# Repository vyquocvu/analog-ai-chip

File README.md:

# Analog AI Machine

**Design and simulate an analog AI accelerator from first principles — from Ohm's law and SPICE circuits to crossbar tiles, language-model inference, and dedicated pocket hardware appliances.**

The repository is built around one engineering question:

> Can the proposed analog AI architecture plausibly operate as a physical device, and can every system-level parameter be traced back to circuit/device evidence or an explicitly labeled assumption?

The project does not claim silicon verification. It builds a reproducible proof chain:

```text
equation
  ↓
functional reference
  ↓
circuit design
  ↓
ngspice / Xyce
  ↓
validated device profiles
  ↓
profile-driven accelerator
  ↓
Transformer / LLM inference
  ↓
physical feasibility report
  ↓
pocket appliance correlation
```

## Current status

The repository contains a broad functional and simulation chain. R9, R17, and
R18 remain open where physical artifacts or measurements are still missing:

```text
R0 functional + circuit foundation ── COMPLETE
R1 circuit → profile → simulator   ── COMPLETE  (crossbar-column-v1)
R2 converter signal path           ── COMPLETE  (dac-r2r-v1, adc-sar-v1)
R3 small crossbar arrays           ── COMPLETE  (0012 2×2 + 0013 4×4, behavioral-equivalence report)
R4 device realism + crossbar-v1    ── COMPLETE  (crossbar-v1, 2D mesh, variation, IR drop, RC settling, drift/faults)
R5 profile-driven physical tile    ── COMPLETE  (calibrated tile, spatial partial sums, error attribution)
R6 accelerator architecture        ── COMPLETE  (scheduler, SRAM buffers, 2D mesh NoC, unified physical ledger)
R7 Transformer & LLM validation    ── PASSED    (TinyGPT/GPT-2 inference, 3-stage hardware recovery, 129.5 PPL)
R8 physical feasibility report     ── PASSED    (latency 998 ns, energy 29.1 nJ/tok, area 1.412 mm², thermal 30.9°C)
R9 implementation correlation      ── PARTIAL   (FPGA shell; physical PCB/bench evidence pending)
R10 scalable model contract        ── PASSED    (manifest, decoder primitives, sharded checkpoints)
R11 memory-bounded simulator       ── PASSED    (block streaming, sampled/surrogate modes, resumable evaluator)
R12 large-model architecture       ── PASSED    (residency, 2.5D multi-die, prefill/decode, KV hierarchy)
R13 large-model validation         ── PASSED    (frozen corpus eval, error attribution, scalable recovery suite)
R14 multi-tier feasibility         ── PASSED    (parametric ledger, Pareto sweeps, 28nm tape-out decision)
R15 physical layout & DRC/LVS      ── PARTIAL   (geometric models; connectivity LVS and physical signoff pending)
R16 post-layout PEX & STA signoff  ── PARTIAL   (assumed analytical models; corrected settling misses aperture)
R17 tape-out & package/PCB signoff ── PARTIAL   (analytical models; physical artifacts pending)
R18 pocket AI communicator / pager ── PARTIAL   (placeholder carrier; electrical implementation incomplete)
```

The strongest claims and their remaining evidence gaps are tracked in
[`docs/ROADMAP.md`](docs/ROADMAP.md) and
[`docs/CURRICULUM.md`](docs/CURRICULUM.md).

---

## Pocket Analog AI Communicator (Pager-1)

Gate R18 implements the dedicated offline text appliance concept: an ultra-low-power pocket communicator ("AI Pager / Beeper") that couples a digital host controller with a 28nm ReRAM Analog Compute-in-Memory Neural Engine.

| Parameter | Specification | Real-World Significance |
| :--- | :--- | :--- |
| **Chassis & Form Factor** | $72.0 \times 54.0 \times 14.5\text{ mm}$ ($85\text{ g}$) | CNC anodized aluminum 6061-T6 with spring-steel belt clip |
| **Reflective Display** | 2.7" Sharp LS027B7DH01 ($400 \times 240$) | Sharp lists **$175\,\mu\text{W}$** for its specified update pattern; standby remains assumed |
| **Input Subsystem** | 35-key tactile QWERTY + Jog Dial | Metal dome tactile switches ($160\text{ gf}$) with I2C scanner (`TCA8418`) |
| **Host Controller** | STM32U575VGT6 Cortex-M33 | Rev A selection; local tokenization and accelerator framing |
| **Battery Autonomy** | $1200\text{ mAh}$ Li-Po ($4.44\text{ Wh}$) | Representative budget: **958 days standby**, **99.8 hours active**; hardware validation pending |
| **Thermal Dissipation** | $25.4^\circ\text{C}$ surface temperature | 100% natural passive convection ($<45.0^\circ\text{C}$ skin touch limit) |
| **Bench Correlation** | Pending | Existing numerical sweep is representative synthetic data, not a measurement |

### Hardware Architecture & Silicon Teardown

---

## Engineering hierarchy

```text
Math / ideal reference
        ↓
Circuit primitives
        ↓
SPICE-verified current-mode crossbar
        ↓
Circuit-to-profile extraction
        ↓
DAC / ADC signal path
        ↓
Small crossbar arrays
        ↓
Device realism + variation
        ↓
Profile-driven tile
        ↓
Multi-tile accelerator + data movement
        ↓
Transformer / LLM mapping
        ↓
Latency / energy / area feasibility
        ↓
FPGA / PCB / silicon correlation
```

See [`docs/CURRICULUM.md`](docs/CURRICULUM.md) for the canonical chapter sequence and [`docs/ROADMAP.md`](docs/ROADMAP.md) for implementation gates.

## Simulation stack

- **KiCad** — schematic and later PCB/layout design artifacts.
- **ngspice** — default SPICE backend for circuit verification, sweeps, transient/noise analysis and compact models.
- **PySpice** — Python automation, assertions, extraction and reproducible experiment orchestration.
- **Xyce** — large-array / parallel SPICE backend when ngspice becomes impractical.
- **NumPy / PyTorch** — functional references, architecture simulation, model mapping and accuracy studies.

See [`docs/SIMULATION_STACK.md`](docs/SIMULATION_STACK.md).

---

## Track 1 — Sequential design book (`book/`)

| # | Topic | Status | Path |
|---|---|---|---|
| 0000 | System and verification boundaries | done | `book/0000-what-we-are-building/` |
| 0001 | Ohm + Kirchhoff = MVM | done | `book/0001-crossbar-mvm/` |
| 0002 | Signed differential weights | done | `book/0002-differential-pairs/` |
| 0003 | DAC/ADC quantization and noise | done | `book/0003-converters-and-noise/` |
| 0004 | Tiling a matrix across arrays | done | `book/0004-tiling/` |
| 0005 | One analog neuron — SPICE | done | `book/0005-one-analog-neuron/` |
| 0006 | Many neurons / scaling | done | `book/0006-many-neurons/` |
| 0007 | Current-mode differential crossbar column | done | `book/0007-crossbar-column/` |
| 0008 | Circuit evidence → device profile | done | `verification/circuit/` + `device_profiles/` |
| 0009 | DAC architecture | done | `book/0009-dac-r2r/` |
| 0010 | ADC / TIA output path | done | `book/0010-adc-sar/` |
| 0011 | Converter variation | done | `book/0011-converter-variation/` |
| 0012 | 2×2 differential crossbar | done | `book/0012-crossbar-2x2/` |
| 0013 | 4×4 differential crossbar | done | `book/0013-crossbar-4x4/` |
| 0014 | Array timing and loading | done | `book/0014-array-timing/` |
| 0015 | Programmable conductance compact model | done | `book/0015-conductance-model/` |
| 0016 | Programming and read variation | done | `book/0016-variation/` |
| 0017 | IR drop and line resistance | done | `book/0017-ir-drop/` |
| 0018 | Parasitic capacitance and RC settling | done | `book/0018-parasitics/` |
| 0019 | Drift, stuck states and non-linearity | done | `book/0019-drift-faults/` |
| 0020 | Crossbar-v1 profile and Gate R4 close | done | `book/0020-crossbar-v1/` |
| 0021 | Physical tile contract | done | `book/0021-physical-tile-contract/` |
| 0022 | Partial sums | done | `book/0022-partial-sums/` |
| 0023 | Scheduler and temporal reuse | done | `book/0023-scheduler/` |
| 0046 | Architecture-neutral model manifest | done | `book/0046-model-manifest/` |
| 0047 | Reusable decoder primitives | done | `book/0047-decoder-primitives/` |
| 0068 | PCIe Gen5 evaluation carrier board signoff | done | `book/0068-pcie-gen5-carrier-board-signoff/` |
| 0069 | Pager-1 product architecture & power ledger | done | `book/0069-pager-product-architecture/` |
| 0070 | Host-to-CiM binary packet protocol & runtime | done | `book/0070-pager-packet-protocol/` |
| 0071 | Pocket carrier PCB & bench correlation | done | `book/0071-pager-hardware-correlation/` |

> See [`docs/CURRICULUM.md`](docs/CURRICULUM.md) for the complete index of all 72 chapters (0000–0071). Every chapter has a bilingual `README.vi.md` beside `README.md`.

## Track 2 — Analog LLM architecture simulator (`analog_llm/`)

A decoder-only transformer runs end to end in software. Dense matrix-vector operations are routed through simulated crossbar tiles; layer norm, softmax, GELU, residual/bias operations and embeddings remain digital.

```text
Prompt tokens
     ↓
Token embedding (digital table)
     ↓
┌────────────────────────────────────────────────────────┐
│ Transformer layer × N                                  │
│   ├── RMSNorm / LayerNorm (digital FP32)               │
│   ├── QKV projection (analog CrossbarTiles)            │
│   ├── Scaled dot-product attention + KV cache (digital)│
│   ├── Output projection (analog CrossbarTiles)         │
│   ├── Residual addition (digital FP32)                 │
│   ├── RMSNorm / LayerNorm (digital FP32)               │
│   ├── MLP / Feed-Forward up+gate (analog CrossbarTiles)│
│   ├── GELU / SiLU activation (digital FP32)            │
│   ├── MLP down projection (analog CrossbarTiles)       │
│   └── Residual addition (digital FP32)                 │
└────────────────────────────────────────────────────────┘
     ↓
Final norm + LM head (analog or digital)
     ↓
Greedy / top-p sampler → next token
```

## Track 3 — Device profiles (`device_profiles/`)

Every physical claim made by the simulator must consume a machine-readable profile derived from KiCad/ngspice/Xyce verification, a validated analytical derivation, or an explicitly stated sensitivity-study assumption.

Evidence classes:

- `measured` — physical hardware measurement;
- `spice` — extracted from a named circuit simulation;
- `derived` — calculated from traceable evidence;
- `assumed` — sensitivity-study input only.

The repository contains the validated SPICE-backed profiles `crossbar-column-v1`, `crossbar-v1`, `dac-r2r-v1` and `adc-sar-v1`, all consumed by `analog_llm` through `profile_adapter` (fail-closed: `assumed`/functional-only evidence cannot support a physical claim). The active milestone is the architecture-neutral model contract and checkpoint-ingestion path for larger models (roadmap R10).

## Verification evidence

Preferred evidence chain:

```text
source schematic/netlist/model
      + deterministic script
      + machine-readable result
      + generated figure
      + validated device profile
      + downstream consumer test
```

A plot without reproducible source/result data is not sufficient evidence.

## Python Environment Setup Guide

### 1. Prerequisites
- **Python 3.9+** (`python3 --version`)
- **Git** (`git --version`)
- *(Optional for circuit SPICE sweeps)*: `ngspice` / `libngspice`

### 2. Step-by-Step Installation

#### Step 1: Clone the repository
```bash
git clone https://github.com/vyquocvu/analog-ai-chip.git
cd analog-ai-chip
```

#### Step 2: Create and activate a virtual environment
- **macOS / Linux**:
  ```bash
  python3 -m venv .venv
  source .venv/bin/activate
  ```
- **Windows (PowerShell)**:
  ```powershell
  python -m venv .venv
  .venv\Scripts\Activate.ps1
  ```

#### Step 3: Install Python dependencies

Choose the target configuration for your workflow:

- **Core & Development** (Unit tests, linter, NumPy, model simulation):
  ```bash
  pip install --upgrade pip
  pip install -e '.[dev]'
  ```

- **Full Simulation Stack** (Adds PySpice for circuit simulation and extraction):
  ```bash
  pip install -e '.[dev,sim]'
  ```

#### Step 4: (Optional) Install `ngspice` for Circuit Simulation
If running or extracting SPICE netlists (`book/0005`–`0014`, `verification/circuit/`):

- **macOS (Homebrew)**:
  ```bash
  brew install libngspice ngspice
  ```
  *(The codebase automatically detects `/opt/homebrew/lib/libngspice.dylib` or `/usr/local/lib/libngspice.dylib`)*

- **Ubuntu / Debian**:
  ```bash
  sudo apt-get update && sudo apt-get install -y libngspice0-dev ngspice
  ```

### 3. Verify Installation

Run the test suite and quality checks:
```bash
# 1. Run all unit tests (233 tests across math, circuits, profiles, and LLM)
pytest

# 2. Run code style & static analysis
ruff check .

# 3. Execute the profile-driven TinyGPT analog accelerator simulation
python scripts/run_llm_sim.py
```

## Honesty principles

- Keep *functional*, *circuit/device*, and *system* claims separate.
- Never describe NumPy/PyTorch execution as physical analog acceleration.
- Never infer end-to-end `O(1)` latency from one resident crossbar operation.
- Never turn an assumed ADC/crossbar parameter into a verified hardware claim.
- Every feasibility report must identify what is simulated, derived, assumed, and measured.

Until physical measurements exist, the strongest supported status is **simulation-backed physical feasibility**, not silicon verification.

## License

MIT. See [LICENSE](LICENSE).

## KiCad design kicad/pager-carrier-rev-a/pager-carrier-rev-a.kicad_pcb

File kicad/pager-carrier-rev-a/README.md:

# Pager-1 Carrier Rev A

This directory contains the editable KiCad 10 source for the 70 mm × 52 mm,
four-layer Pager-1 main carrier. The display, keypad, protected Li-Po pack, and
analog accelerator are external assemblies.

## Evidence boundary

Status: `INCOMPLETE_CARRIER_DESIGN`. Do not fabricate this placeholder as a
working product. Subsystem sheets contain text only, most components are
unconnected, and generated footprints do not implement the declared packages.
The BOM lacks the PMIC inductor and capacitors. Clean ERC/DRC on passive,
no-connect symbols does not establish electrical completeness.

The historical evidence record omits subsheets and local libraries and is now
rejected by the source-inventory check. Manufacturing export is also blocked by
BOM footprint mismatches. The preliminary impedance estimate remains `assumed`.
See `SOURCE_NOTES.md` for manufacturer references; startup and pin assignments
still require circuit implementation and verification.

The authoritative electrical/mechanical contract is
`hardware-manifest.json`. In particular, pins named `NC_RESERVED_*` must not be
connected and pins named `TEST_ONLY_*` are diagnostic inputs, not production
interfaces.

## Project files

- `pager-carrier-rev-a.kicad_pro`: project settings.
- `pager-carrier-rev-a.kicad_sch`: hierarchy overview.
- `power.kicad_sch`, `host.kicad_sch`, `display.kicad_sch`,
  `input-haptics.kicad_sch`, `accelerator-mezzanine.kicad_sch`: subsystem
  text-only placeholder sheets.
- `pager-carrier-rev-a.kicad_pcb`: partially routed placeholder layout.
- `pager-carrier-rev-a.kicad_dru`: project design rules.
- `Pager.kicad_sym`, `Pager.pretty/`, and the library tables: project-local
  source for the custom connector symbol and land pattern. Project schematics
  and the routed board also embed their generated library copies.

## Validation and manufacturing exports

KiCad 10.0.x is required. Run:

```bash
python scripts/build_pager_kicad.py --kicad-cli /path/to/kicad-cli
```

The command runs ERC and DRC with violation exit codes, exports BOM, Gerbers,
drill and placement data, PDF documentation, STEP, and front/back renders,
then writes a deterministic release manifest beneath `build/kicad/pager-carrier-rev-a/`.
Generated manufacturing files are intentionally not committed.

## Power-up constraint

BQ25120A starts its SYS buck at 1.8 V. Firmware must boot from internal MCU
flash, program SYS to 3.3 V, verify it, and only then enable the switched 2.5 V,
1.0 V, and LCD 5 V rails. `ACCEL_RESET_N` remains asserted during this sequence.

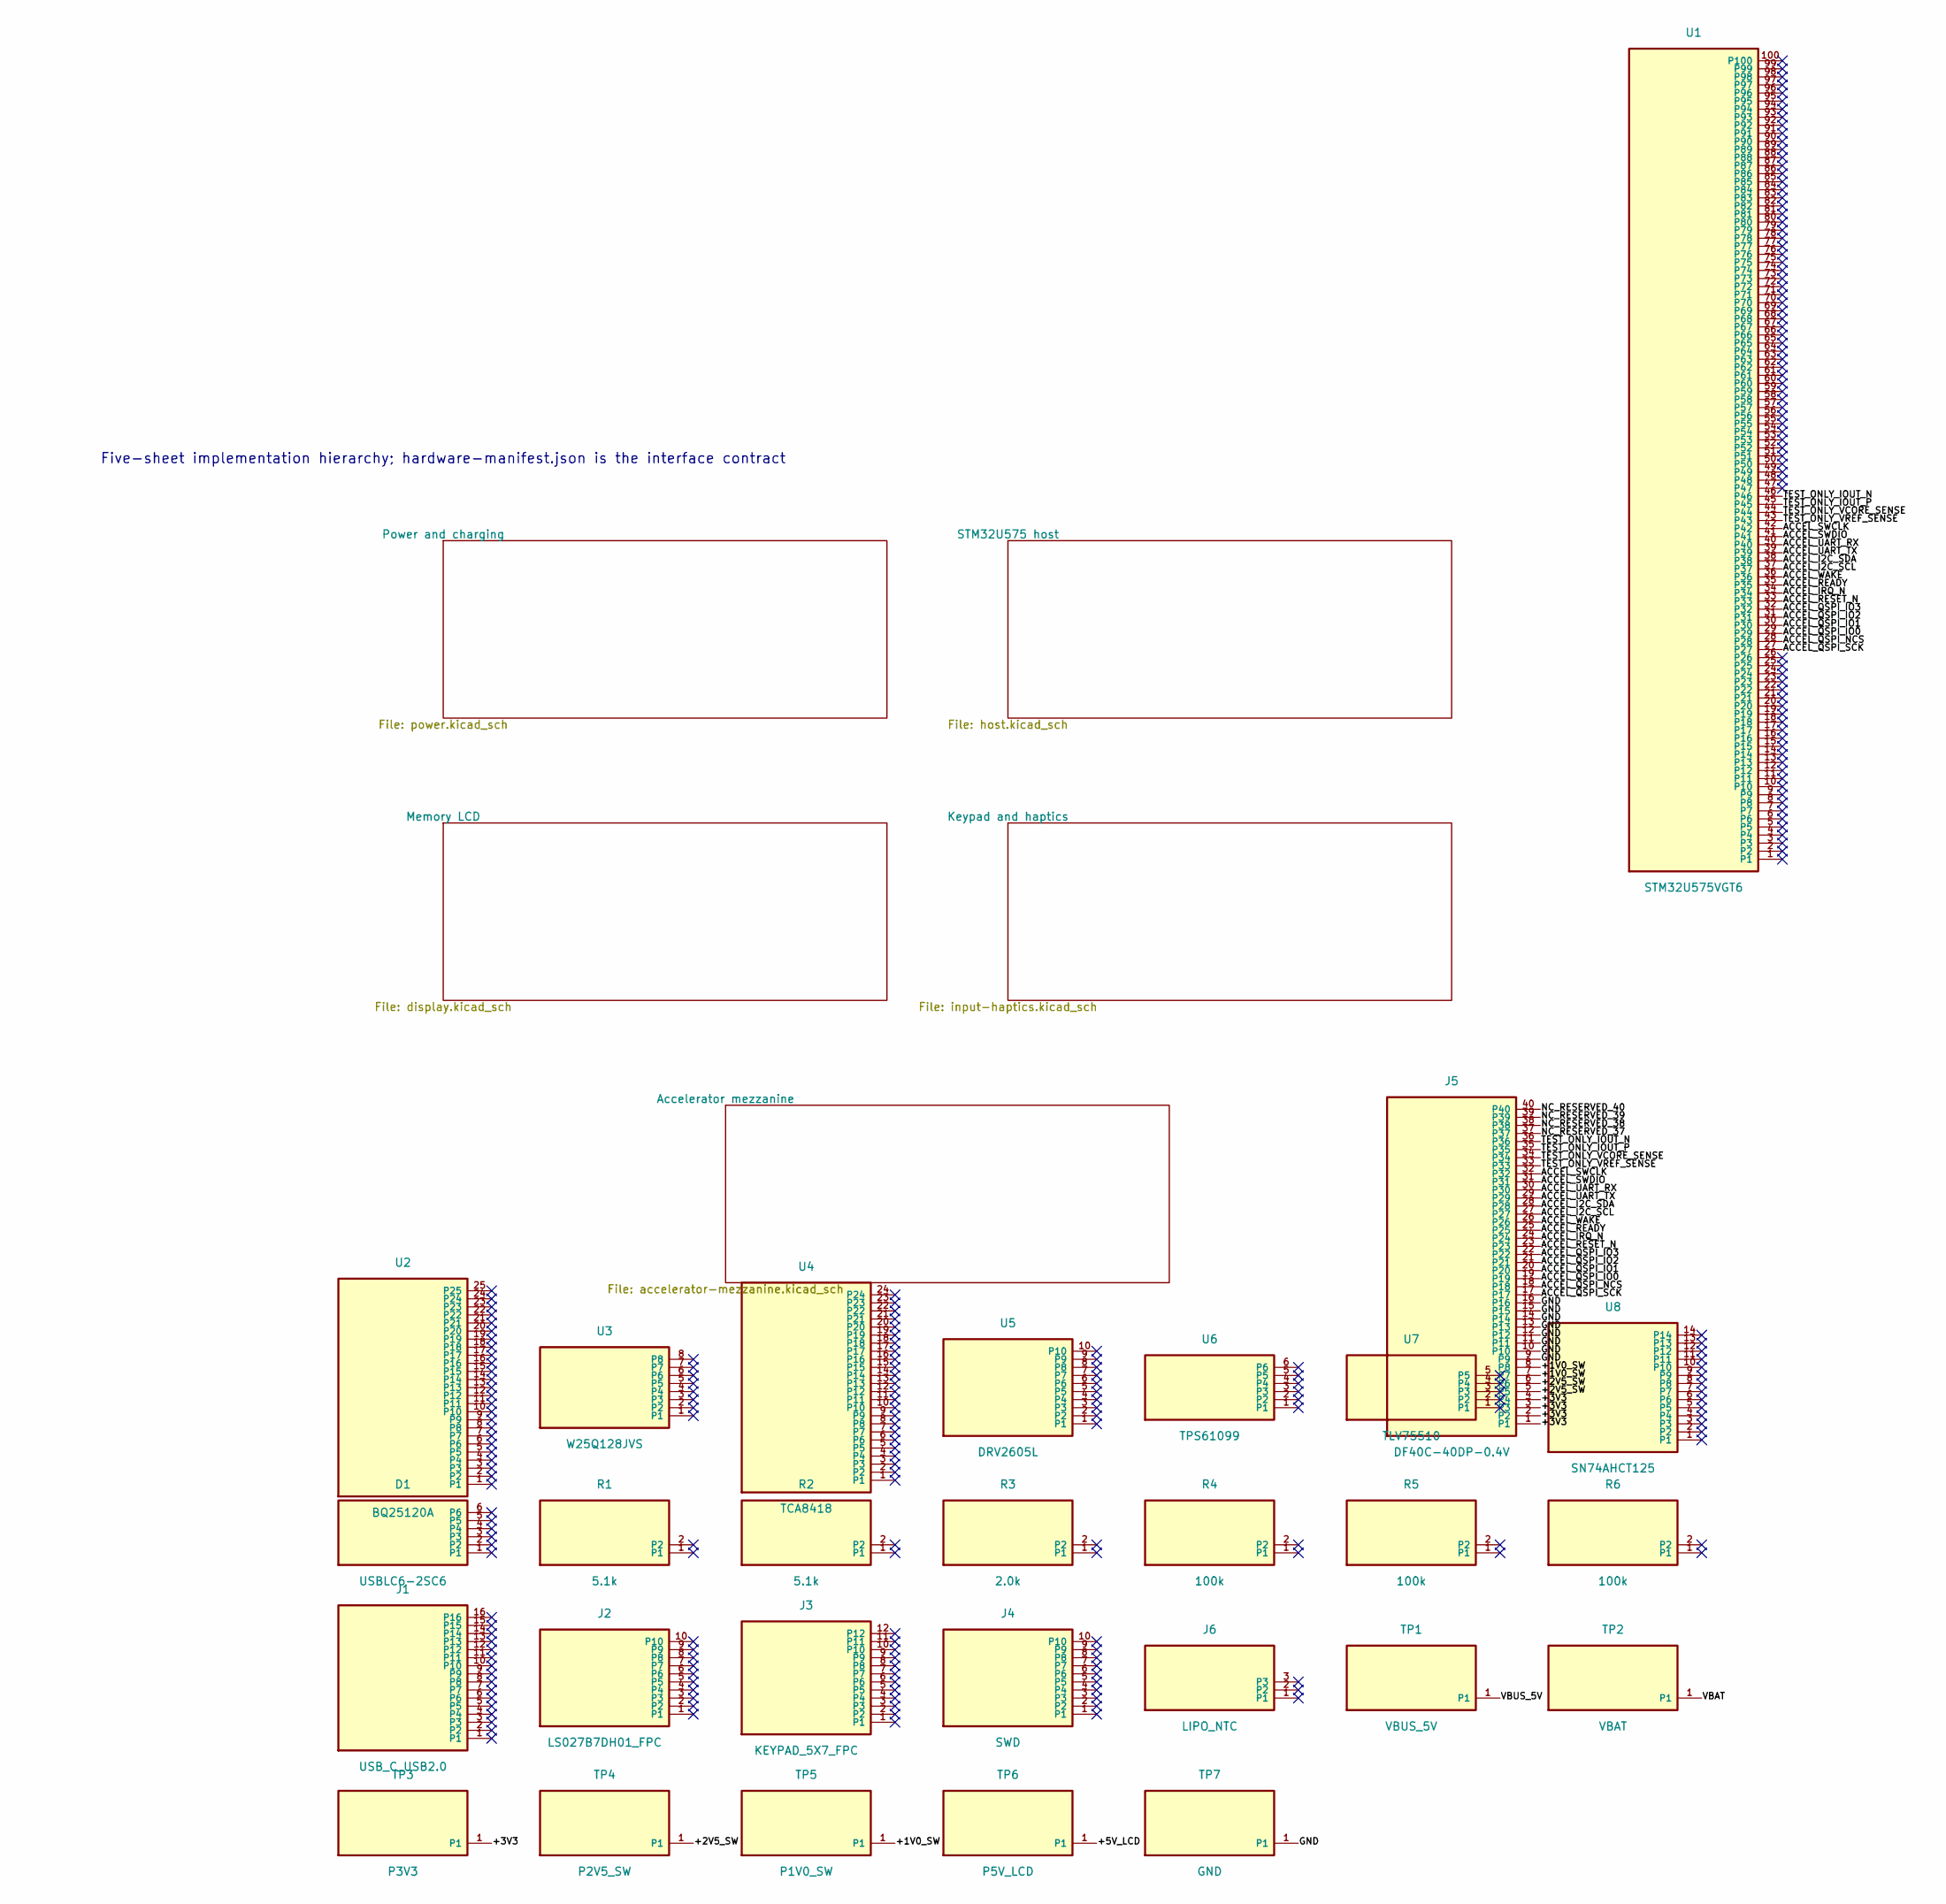
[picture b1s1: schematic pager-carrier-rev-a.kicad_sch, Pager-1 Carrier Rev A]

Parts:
D1: USBLC6-2SC6; MPN USBLC6-2SC6
J1: USB_C_USB2.0; MPN USB4105-GF-A
J2: LS027B7DH01_FPC; MPN FH12-10S-0.5SH(55)
J3: KEYPAD_5X7_FPC; MPN FH12-12S-0.5SH(55)
J4: SWD; MPN FTSH-105-01-L-DV-K
J5: DF40C-40DP-0.4V; MPN DF40C-40DP-0.4V(51)
J6: LIPO_NTC; MPN S3B-PH-K-S
R1, R2: 5.1k; MPN RC0402FR-075K1L
R3: 2.0k; MPN RC0402FR-072KL
R4, R5, R6: 100k; MPN RC0402FR-07100KL
TP1: VBUS_5V
TP2: VBAT
TP3: P3V3
TP4: P2V5_SW
TP5: P1V0_SW
TP6: P5V_LCD
TP7: GND
U1: STM32U575VGT6; MPN STM32U575VGT6
U2: BQ25120A; MPN BQ25120AYFPR
U3: W25Q128JVS; MPN W25Q128JVSIQ
U4: TCA8418; MPN TCA8418RTWR
U5: DRV2605L; MPN DRV2605LDGSR
U6: TPS61099; MPN TPS61099DRVR
U7: TLV75510; MPN TLV75510PDBVR
U8: SN74AHCT125; MPN SN74AHCT125PWR

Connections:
/+1V0_SW: J5.7, J5.8, TP5.1
/+2V5_SW: J5.5, J5.6, TP4.1
/+3V3: J5.1, J5.2, J5.3, J5.4, TP3.1
/+5V_LCD: TP6.1
/ACCEL_I2C_SCL: J5.27, U1.37
/ACCEL_I2C_SDA: J5.28, U1.38
/ACCEL_IRQ_N: J5.24, U1.34
/ACCEL_QSPI_IO0: J5.19, U1.29
/ACCEL_QSPI_IO1: J5.20, U1.30
/ACCEL_QSPI_IO2: J5.21, U1.31
/ACCEL_QSPI_IO3: J5.22, U1.32
/ACCEL_QSPI_NCS: J5.18, U1.28
/ACCEL_QSPI_SCK: J5.17, U1.27
/ACCEL_READY: J5.25, U1.35
/ACCEL_RESET_N: J5.23, U1.33
/ACCEL_SWCLK: J5.32, U1.42
/ACCEL_SWDIO: J5.31, U1.41
/ACCEL_UART_RX: J5.30, U1.40
/ACCEL_UART_TX: J5.29, U1.39
/ACCEL_WAKE: J5.26, U1.36
/GND: J5.9, J5.10, J5.11, J5.12, J5.13, J5.14, J5.15, J5.16, TP7.1
/NC_RESERVED_37: J5.37
/NC_RESERVED_38: J5.38
/NC_RESERVED_39: J5.39
/NC_RESERVED_40: J5.40
/TEST_ONLY_IOUT_N: J5.36, U1.46
/TEST_ONLY_IOUT_P: J5.35, U1.45
/TEST_ONLY_VCORE_SENSE: J5.34, U1.44
/TEST_ONLY_VREF_SENSE: J5.33, U1.43
/VBAT: TP2.1
/VBUS_5V: TP1.1

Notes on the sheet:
Five-sheet implementation hierarchy; hardware-manifest.json is the interface contract

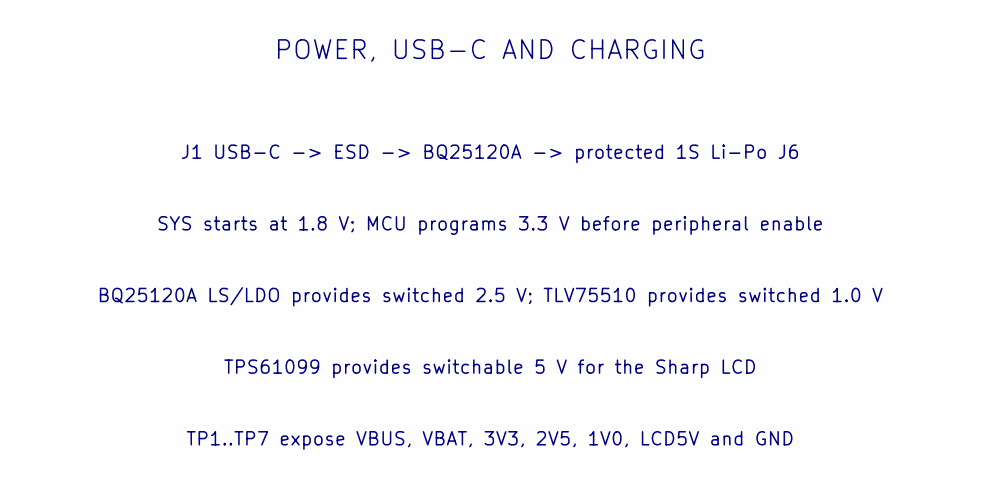
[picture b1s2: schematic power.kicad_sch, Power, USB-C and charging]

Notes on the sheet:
POWER, USB-C AND CHARGING
J1 USB-C -> ESD -> BQ25120A -> protected 1S Li-Po J6
SYS starts at 1.8 V; MCU programs 3.3 V before peripheral enable
BQ25120A LS/LDO provides switched 2.5 V; TLV75510 provides switched 1.0 V
TPS61099 provides switchable 5 V for the Sharp LCD
TP1..TP7 expose VBUS, VBAT, 3V3, 2V5, 1V0, LCD5V and GND

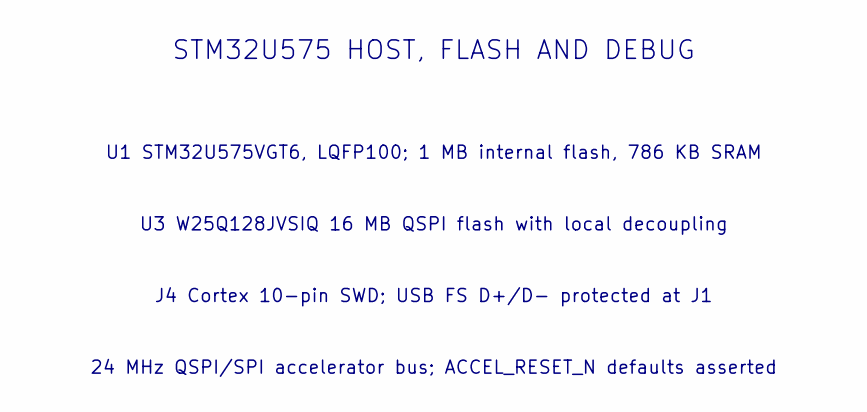
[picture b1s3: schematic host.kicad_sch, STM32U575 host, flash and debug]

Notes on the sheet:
STM32U575 HOST, FLASH AND DEBUG
U1 STM32U575VGT6, LQFP100; 1 MB internal flash, 786 KB SRAM
U3 W25Q128JVSIQ 16 MB QSPI flash with local decoupling
J4 Cortex 10-pin SWD; USB FS D+/D- protected at J1
24 MHz QSPI/SPI accelerator bus; ACCEL_RESET_N defaults asserted

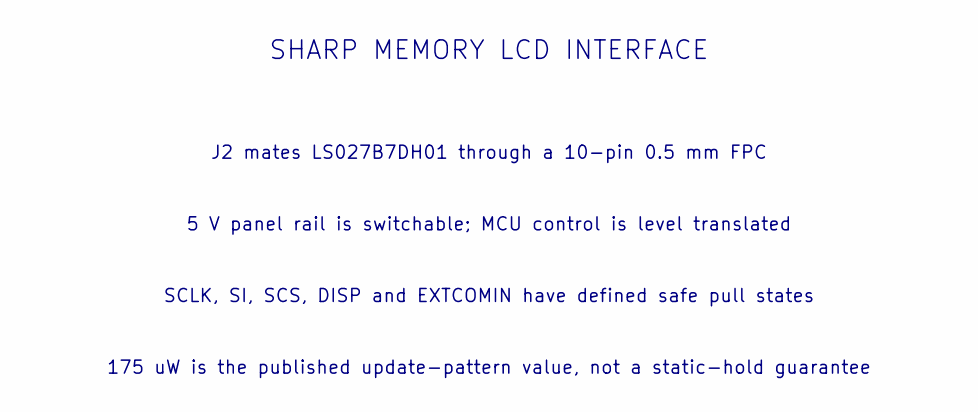
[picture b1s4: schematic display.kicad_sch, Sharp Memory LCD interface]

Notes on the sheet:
SHARP MEMORY LCD INTERFACE
J2 mates LS027B7DH01 through a 10-pin 0.5 mm FPC
5 V panel rail is switchable; MCU control is level translated
SCLK, SI, SCS, DISP and EXTCOMIN have defined safe pull states
175 uW is the published update-pattern value, not a static-hold guarantee

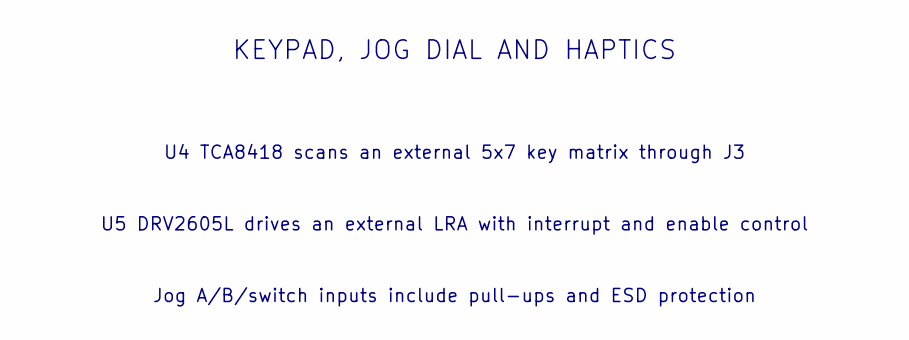
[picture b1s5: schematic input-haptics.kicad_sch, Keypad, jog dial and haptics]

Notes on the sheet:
KEYPAD, JOG DIAL AND HAPTICS
U4 TCA8418 scans an external 5x7 key matrix through J3
U5 DRV2605L drives an external LRA with interrupt and enable control
Jog A/B/switch inputs include pull-ups and ESD protection

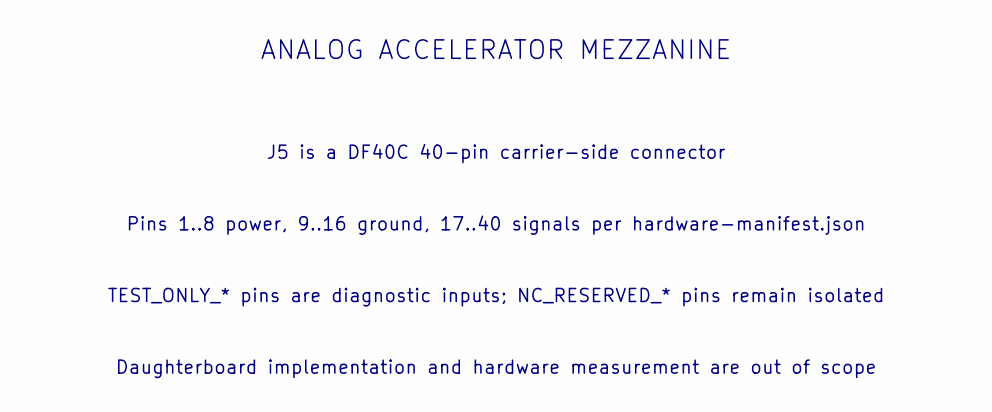
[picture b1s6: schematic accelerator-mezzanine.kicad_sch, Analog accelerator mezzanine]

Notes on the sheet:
ANALOG ACCELERATOR MEZZANINE
J5 is a DF40C 40-pin carrier-side connector
Pins 1..8 power, 9..16 ground, 17..40 signals per hardware-manifest.json
TEST_ONLY_* pins are diagnostic inputs; NC_RESERVED_* pins remain isolated
Daughterboard implementation and hardware measurement are out of scope

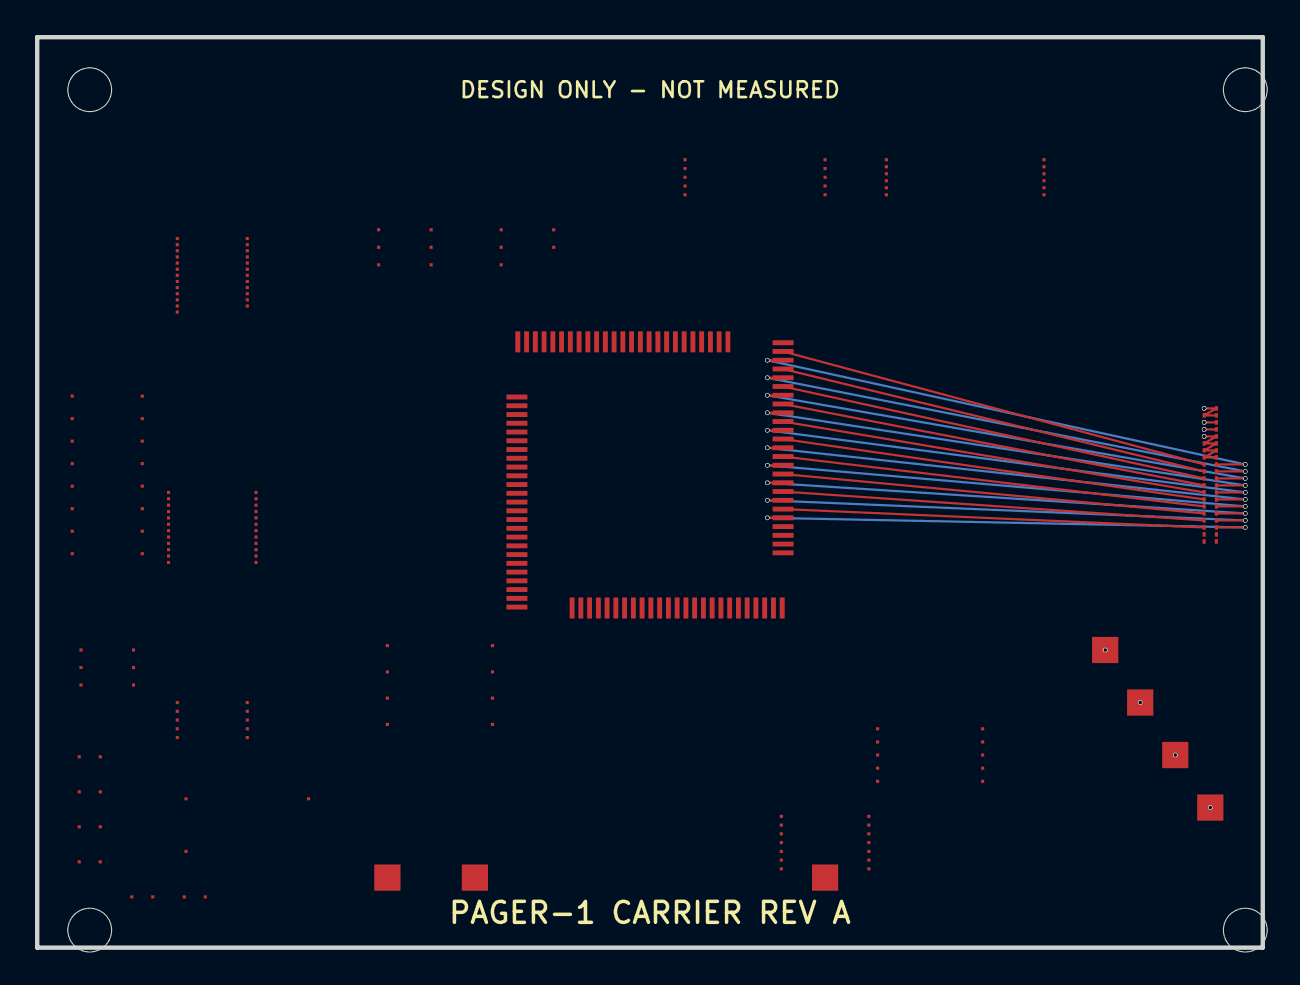
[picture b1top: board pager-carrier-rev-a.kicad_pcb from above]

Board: 4 copper layers, 70.0 x 52.0 mm, 32 parts (0 on the bottom side), 24 nets.

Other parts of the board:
H1, H2, H3, H4: MountingHole_2.5mm
